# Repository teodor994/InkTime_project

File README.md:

<h1 align="center">InkTime Watch</h1>

<br>
<br>

This document presents the design and implementation details of the InkTime smartwatch project, covering both the hardware architecture and mechanical integration.

In the following sections, you will find comprehensive documentation including the schematic, PCB layout, component selection, and 3D assembly of the device.

<br> 

## Block Diagram

```text

                                +----------------------+
                                |        USB-C         |
                                |   Power / USB Data   |
                                +----------+-----------+
                                           |
                                           v
                                +----------------------+
                                |   ESD Protection     |
                                |    USBLC6-2SC6Y      |
                                +----------+-----------+
                                           |
                                           v
                                +----------------------+
                                |   Li-Po Charger      |
                                |    BQ25180YBGR       |
                                +----+------------+----+
                                     |            |
                                     |            +--------------------+
                                     |                                 |
                                     v                                 v
                           +-------------------+             +-------------------+
                           |   Li-Po Battery   |             |   Fuel Gauge      |
                           |     LP502030      |<-- I2C ---> |    MAX17048       |
                           +---------+---------+             +-------------------+
                                     |
                                     v
                           +-------------------+
                           | Buck-Boost DC/DC  |
                           |    RT6160AWSC     |
                           +---------+---------+
                                     |
                                   3V3 / VREG
                                     |
        +----------------------------+------------------------------+
        |                            |                              |
        v                            v                              v
+---------------+          +-------------------+          +-------------------+
|   nRF52840    |<--I2C--->|      BMA421       |<--I2C--->|     DRV2605       |
|   BLE MCU     |          |       IMU         |          |   Haptic Driver   |
+-------+-------+          +-------------------+          +---------+---------+
        |                                                              |
        | SPI + GPIO                                                    v
        v                                                      +----------------+
+-------------------+                                          | Vibration Motor|
| 1.54" E-Paper     |                                          |     (Shaker)   |
| via FPC Connector |                                          +----------------+
+-------------------+
        |
        +--> Dedicated E-Paper Power Stage:
             MOSFETs + Schottky Diodes + Inductors + Capacitors

```

## Hardware Functionality

###  Microcontroller

The system is built around a Nordic **nRF52840** SoC  
*(Arm Cortex-M4F @ 64 MHz, 1 MB Flash, 256 kB RAM)*.

This component was chosen because it integrates:
- a **2.4 GHz radio (Bluetooth Low Energy)**
- a **USB 2.0 full-speed controller**

 This allows both:
- wireless communication (BLE)
- USB-C data connectivity  

without requiring any external transceiver.

The MCU operates using two external crystals:
- **32 MHz HF crystal (XC1/XC2)** → CPU + radio
- **32.768 kHz LF crystal (XL1/XL2)** → RTC + low-power timing  

> Accurate timekeeping is critical for a watch, therefore the LFXO is mandatory.

An on-board **2.4 GHz chip antenna (2450AT18B100E)** is:
- placed at the edge of the PCB  
- isolated via a **ground keep-out zone**  

The antenna is connected to the `ANT` pin through a matching network.

---

### Display — E-Paper (SPI)

A reflective **e-paper display** is controlled via the SPI interface:

- `SCK` → P0.02  
- `MOSI` → P0.03  
- `CS` → P0.05  

Additional control signals:
- `EPD_DC` (P0.15) → command/data selection  
- `EPD_RST` (P0.16) → hardware reset  
- `EPD_BUSY` (P0.17) → busy status input  

The display is connected using a **24-pin FPC connector**.

#### Power Optimization
E-paper displays consume power **only during refresh**.

To optimize energy consumption:
- the display power rail is gated using a **PFET**
- controlled by `P1.01`

This allows:
- complete power shutdown between updates  
- significantly extended battery life (days instead of hours)

---

### IMU — BMA421 (I²C)

The **Bosch BMA421** accelerometer provides:
- 3-axis acceleration data  
- built-in **step counting functionality**

Connected via the shared I²C bus.

Interrupt lines:
- `IMU_INT1` → P0.08  
- `IMU_INT2` → P1.08  

These allow:
- wake-up from deep sleep  
- event-driven processing (no polling required)

---

### Haptics — DRV2605 (I²C)

The **TI DRV2605L** controls a vibration motor (LRA/ERM).

Key features:
- I²C configuration interface  
- internal ROM with predefined haptic effects  

The MCU only sends:
> “play effect N” commands  

instead of generating waveforms.

Control signal:
- `HAPTIC_EN` → P0.12  

Allows full shutdown of the driver when idle.

---

### Power Management  
**BQ25180 + MAX17048 + RT6160**

#### USB Input
- USB-C provides **5V input**
- protected by **USBLC6-2SC6Y (ESD protection)**
- includes **5.1 kΩ CC pull-down resistors** → device configured as sink

---

#### Battery Charging — BQ25180
Handles:
- Li-Po charging (CC/CV)
- power path management (USB ↔ battery switching)

Communication:
- I²C interface
- interrupt line: `PMIC_INT` → P0.11  

---

#### Voltage Regulation — RT6160
- Buck-boost converter generating stable **3.3V (VREG)**

Why buck-boost:
- battery range: **3.0V – 4.2V**
- ensures stable output across full discharge cycle

---

#### Fuel Gauge — MAX17048
Provides:
- battery percentage
- voltage monitoring

Uses **ModelGauge algorithm**:
- no current sense resistor required

Communication:
- I²C interface  
- `ALERT` → P1.10 (threshold events)

---

### Inputs — Buttons

Three user buttons connected as:
- `P0.13`
- `P0.14`
- `P1.02`

Characteristics:
- active-low configuration  
- RC debounce  
- internal pull-ups used  

Support:
- GPIOTE interrupts  
- wake-up from System OFF

---

### Shared I²C Bus

All I²C peripherals share the same bus:

Devices:
- BMA421 (IMU)
- MAX17048 (fuel gauge)
- DRV2605L (haptics)
- BQ25180 (charger)

Bus lines:
- `SDA` → P0.06  
- `SCL` → P0.07  

Pull-ups:
- **3.3 kΩ to 3V3**

Operating mode:
- **400 kHz (Fast Mode)**

Sufficient for low-bandwidth sensor communication.

---

### Debug Interface

Programming and debugging via SWD:

- `SWDCLK`
- `SWDIO`
- optional `SWO` → P1.00  

Connector:
- **Tag-Connect TC2030 footprint**

Advantage:
- no bulky header required (important for wearable design)

---

### Expected Capabilities

Based on this hardware, the system supports:

- accurate timekeeping using RTC + LFXO  
- rendering UI on e-paper display  
- step detection & gesture sensing  
- haptic feedback via vibration motor  
- BLE communication with a smartphone  
- USB connectivity for power and data  
- real-time battery monitoring  

The design enables a **low-power wearable device** with multi-day battery life.

## Pinout Table

| Pin | Signal | Direction | Peripheral | Description |
|-----|--------|-----------|------------|-------------|
| P0.02 | SPI_SCK | Output | E-Paper Display | SPI clock |
| P0.03 | SPI_MOSI | Output | E-Paper Display | SPI data out |
| P0.05 | EPD_CS | Output | E-Paper Display | Chip select |
| P0.06 | SDA | Bidir | Fuel Gauge, Charger, IMU, Haptics | Shared I2C data |
| P0.07 | SCL | Output | Fuel Gauge, Charger, IMU, Haptics | Shared I2C clock |
| P0.08 | IMU_INT1 | Input | IMU (BMA421) | Interrupt line 1 |
| P0.11 | PMIC_INT | Input | Charger (BQ25180) | Fault/status interrupt |
| P0.12 | HAPTIC_EN | Output | Haptics (DRV2605) | Driver enable |
| P0.13 | — | Input | Button 1 | User button |
| P0.14 | — | Input | Button 2 | User button |
| P0.15 | EPD_DC | Output | E-Paper Display | Data/command select |
| P0.16 | EPD_RST | Output | E-Paper Display | Display reset |
| P0.17 | EPD_BUSY | Input | E-Paper Display | Busy status |
| P0.18 | RESET | Input | — | System reset |
| P1.00 | SWO | Output | Debug (pad) | SWD trace output |
| P1.01 | — | Output | EPD power gate | EPD power control |
| P1.02 | — | Input | Button 3 | User button |
| P1.08 | IMU_INT2 | Input | IMU (BMA421) | Interrupt line 2 |
| P1.10 | ALERT | Input | Fuel Gauge (MAX17048) | UV/OV alert |
| D+ | D+ | Bidir | USB-C connector | USB data+ |
| D− | D- | Bidir | USB-C connector | USB data− |
| XL1/XL2 | — | — | 32.768 kHz crystal | Low-frequency clock |
| XC1/XC2 | — | — | 32 MHz crystal | High-frequency clock |
| SWDCLK | SWDCLK | Input | Debug (pad) | SWD clock |
| SWDIO | SWDIO | Bidir | Debug (pad) | SWD data |
| ANT | RF | Output | 2.4 GHz antenna | Wireless antenna feed |

## Bill of Materials (BOM)

| Part Name | Qty | Link (Order + Datasheet) |
| :-- | :--: | :--: |
| NRF52840-QIAA-R7 | 1 | [Link](https://jlcpcb.com/partdetail/NordicSemicon-NRF52840_QIAAR7/C1851953) |
| BMA421 | 1 | [Link](https://jlcpcb.com/partdetail/BoschSensortec-BMA421/C5242966) |
| DRV2605YZFR | 1 | [Link](https://jlcpcb.com/partdetail/TexasInstruments-DRV2605YZFR/C81079) |
| BQ25180YBGR | 1 | [Link](https://jlcpcb.com/partdetail/TexasInstruments-BQ25180YBGR/C3682423) |
| MAX17048G+T10 | 1 | [Link](https://jlcpcb.com/partdetail/2777647-MAX17048GT10/C2682616) |
| RT6160AWSC | 1 | [Link](https://jlcpcb.com/partdetail/RichtekTech-RT6160AWSC/C7065276) |
| USBLC6-2SC6Y | 1 | [Link](https://jlcpcb.com/partdetail/TECHPUBLIC-USBLC62SC6Y/C5310974) |
| KH-TYPE-C-16P | 1 | [Link](https://jlcpcb.com/partdetail/Shenzhen_KinghelmElec-KH_TYPE_C16P/C709357) |
| 2450AT18B100E | 1 | [Link](https://jlcpcb.com/partdetail/JohansonDielectrics-2450AT18B100E/C2917717) |
| SI1308EDL-T1-GE3 | 1 | [Link](https://jlcpcb.com/partdetail/VishayIntertech-SI1308EDL_T1GE3/C469327) |
| DMG2305UX-7 | 1 | [Link](https://jlcpcb.com/partdetail/DiodesIncorporated-DMG2305UX7/C150470) |
| 5034802400 | 1 | [Link](https://jlcpcb.com/partdetail/MOLEX-5034802400/C122434) |
| EVPAKE31A | 3 | [Link](https://jlcpcb.com/partdetail/PANASONIC-EVPAKE31A/C569760) |
| NX2016SA-32MHZ-STD-CZS-5 | 1 | [Link](https://jlcpcb.com/partdetail/NDK-NX2016SA_32MHZ_STD_CZS5/C843260) |
| CM8V-T1A-32.768KHZ-9PF-20PPM-TB-QA | 1 | [Link](https://jlcpcb.com/partdetail/C5366546) |
| SDFL1608S100KTF | 1 | [Link](https://jlcpcb.com/partdetail/Sunlord-SDFL1608S100KTF/C1035) |
| SDCL1005C15NJTDF | 1 | [Link](https://jlcpcb.com/partdetail/Sunlord-SDCL1005C15NJTDF/C27143) |
| SDCL1005C3N9STDF | 1 | [Link](https://jlcpcb.com/partdetail/Sunlord-SDCL1005C3N9STDF/C14033) |
| FTC252012SR47MBCA | 1 | [Link](https://jlcpcb.com/partdetail/6763488-FTC252012SR47MBCA/C5832368) |
| 744043680 | 1 | [Link](https://jlcpcb.com/partdetail/WurthElektronik-744043680/C2045671) |
| MBR0530 | 3 | [Link](https://jlcpcb.com/partdetail/78464-MBR0530/C77336) |
| GRM033R61A104KE15D | 5 | [Link](https://jlcpcb.com/partdetail/MurataElectronics-GRM033R61A104KE15D/C76934) |
| GRM155R60J226ME11D | 2 | [Link](https://jlcpcb.com/partdetail/408393-GRM155R60J226ME11D/C415703) |
| GRM155R61H105KE05D | 9 | [Link](https://jlcpcb.com/partdetail/1609005-GRM155R61H105KE05D/C1518208) |
| GRM0335C1H1R0BA01D | 2 | [Link](https://jlcpcb.com/partdetail/MurataElectronics-GRM0335C1H1R0BA01D/C85893) |
| GRM0335C1H101JA01D | 1 | [Link](https://jlcpcb.com/partdetail/MurataElectronics-GRM0335C1H101JA01D/C76922) |
| CGA0402X5R475M250GT | 1 | [Link](https://jlcpcb.com/partdetail/HRE-CGA0402X5R475M250GT/C6119795) |
| CL05A475MP5NRNC | 5 | [Link](https://jlcpcb.com/partdetail/24469-CL05A475MP5NRNC/C23733) |
| CL05A105KA5NQNC | 6 | [Link](https://jlcpcb.com/partdetail/53938-CL05A105KA5NQNC/C52923) |
| CL05A106MQ5NUNC | 3 | [Link](https://jlcpcb.com/partdetail/16204-CL05A106MQ5NUNC/C15525) |
| CC0201KRX5R7BB473 | 1 | [Link](https://jlcpcb.com/partdetail/YAGEO-CC0201KRX5R7BB473/C505465) |
| 0201X104K100NT | 5 | [Link](https://jlcpcb.com/partdetail/270391-0201X104K100NT/C284966) |
| 0201WMF220KTEE | 1 | [Link](https://jlcpcb.com/partdetail/479910-0201WMF220KTEE/C473517) |
| 0201WMJ0000TEE | 3 | [Link](https://jlcpcb.com/partdetail/259867-0201WMJ0000TEE/C270337) |
| 0201WMJ0332TEE | 2 | [Link](https://jlcpcb.com/partdetail/259848-0201WMJ0332TEE/C270318) |
| 0201CG120J500NT | 4 | [Link](https://jlcpcb.com/partdetail/51400-0201CG120J500NT/C50391) |
| CR0201FH5101G | 2 | [Link](https://jlcpcb.com/partdetail/LIZElec-CR0201FH5101G/C100142) |
| CPF0201D10KC1 | 6 | [Link](https://jlcpcb.com/partdetail/TEConnectivity-CPF0201D10KC1/C4187156) |
| UCR006YVPFLR470 | 1 | [Link](https://jlcpcb.com/partdetail/ROHMSemicon-UCR006YVPFLR470/C2089071) |

## Design Details

### Schematic and Components

The reference schematic was carefully reviewed and validated against the datasheets of each individual component. Any inconsistencies identified during this process were analyzed and corrected, most of them originating from outdated reference designs used in the initial schematic.

---

### PCB Layout and Routing

The PCB was designed in accordance with the manufacturing constraints specified by JLCPCB for standard rigid PCB assembly.

A ground pour was implemented on the top layer and connected to the main ground plane using via stitching. Additional manual stitching was applied in sensitive areas, particularly around the antenna feed line, to improve signal integrity.

Teardrops were added to most trace junctions to enhance mechanical reliability. Due to limitations in Fusion when generating teardrops for off-grid or rotated components, some shapes—especially those near the MCU (placed at a 45-degree angle)—were manually refined to ensure proper geometry.

Given the limited available space and the minimum recommended silkscreen text size of 1 mm, an indexed labeling approach was used. Larger components, ICs, and important pads were labeled directly on the silkscreen, while smaller areas rely on the legend.

To ensure mechanical robustness, relatively large internal annular rings were maintained. As a consequence, certain unused pins of the MCU were masked to prevent unintended electrical connections with traces routed underneath.

VIA-in-pad (ViP) technology was used extensively for compact multi-pin SMD components. Any DRC warnings related to ViP clearances were manually reviewed and accepted where appropriate.

Special attention was given to spatial constraints such as:
- antenna keep-out zone
- crystal oscillator trace length
- maximizing distance between the IMU and the shaker motor

Additionally, all decoupling capacitors were placed as close as possible to their respective power pins.

The USB differential pair (D+ and D−) was routed carefully, maintaining approximately equal lengths and minimal spacing between the traces to preserve signal integrity.

---

### 3D Design

Accurate 3D models for all components were integrated into the PCB assembly in order to validate the mechanical design.

The complete enclosure assembly was analyzed to detect any potential mechanical interferences. A possible issue was identified regarding the battery height specified in its datasheet, as the available space in the lower part of the enclosure may be insufficient.

At this stage, the enclosure design was left unchanged, with the intention of validating this aspect during the physical prototyping phase.

## Renders

### PCB 2D

### PCB 3D

### Assembly

### Exploded View

### Without Display

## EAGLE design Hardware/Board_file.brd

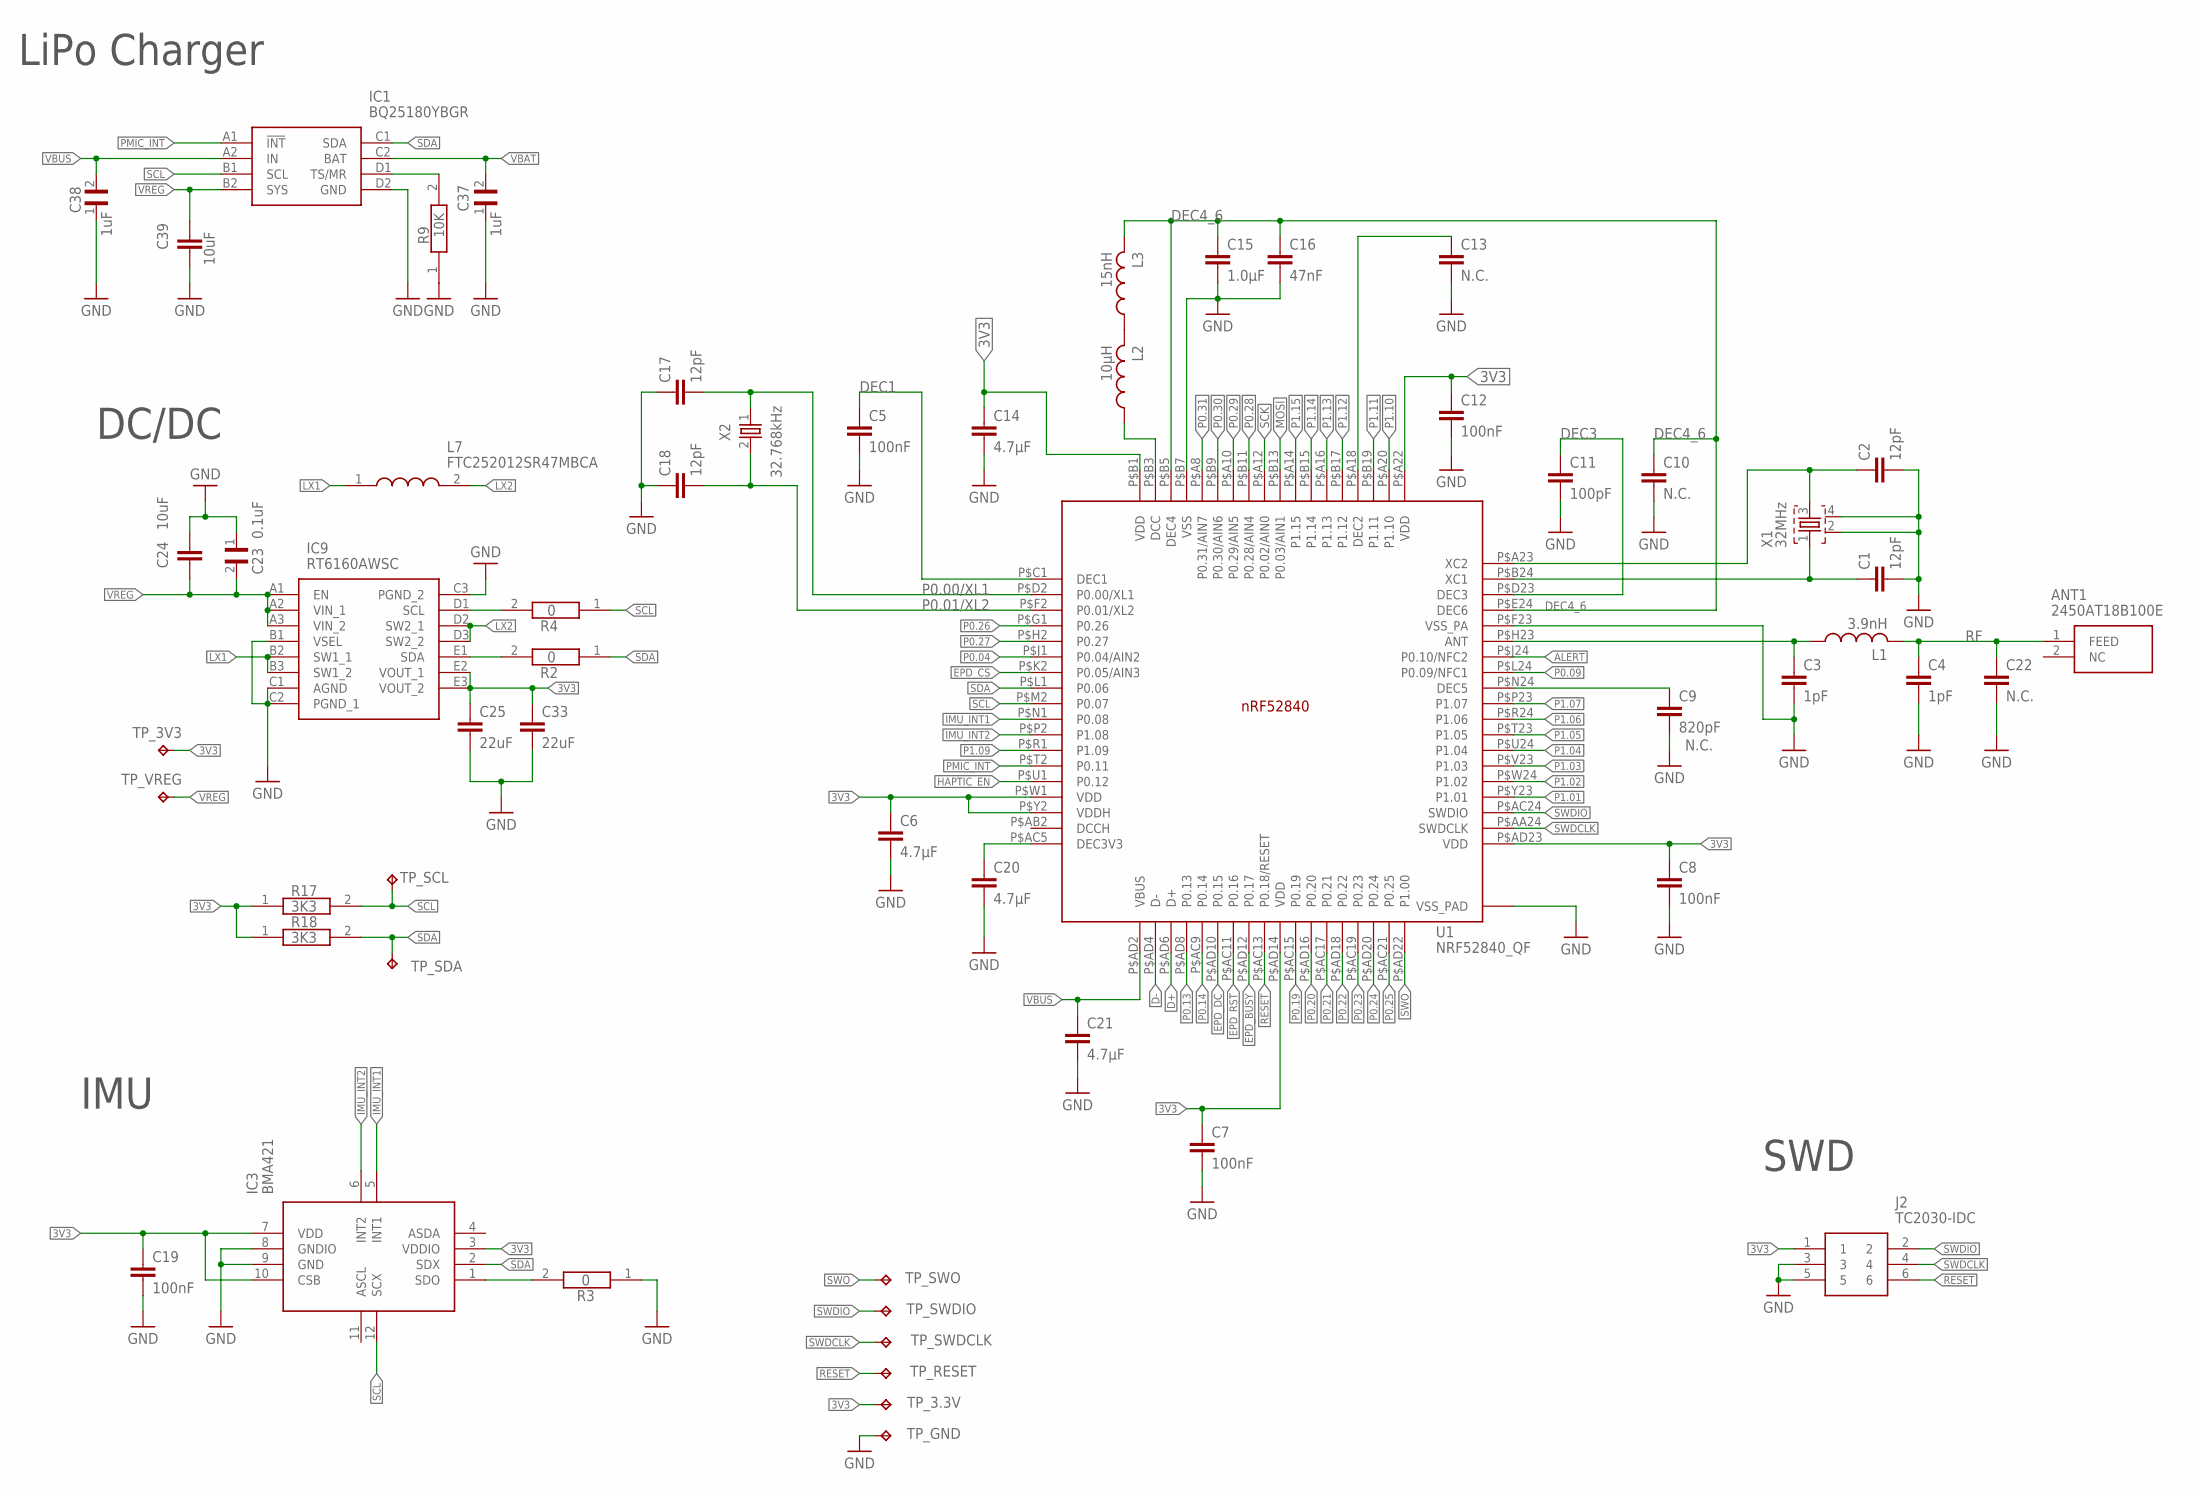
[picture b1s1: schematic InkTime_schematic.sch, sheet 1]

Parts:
ANT1: 2450AT18B100E; 2450AT18B100E_ANTC3216X140N
C1, C2, C17, C18: 12pF; NORDIC_NRF_3_RESC0201_L
C3, C4: 1pF; NORDIC_NRF_3_RESC0201_L
C5, C7, C8, C12, C19: 100nF; NORDIC_NRF_3_RESC0201_L
C6, C14, C20, C21: 4.7µF; NORDIC_NRF_3_RESC0201_L
C9: 820pF; NORDIC_NRF_3_RESC0201_L
C10, C13, C22: N.C.; NORDIC_NRF_3_RESC0201_L
C11: 100pF; NORDIC_NRF_3_RESC0201_L
C15: 1.0µF; NORDIC_NRF_3_RESC0201_L
C16: 47nF; NORDIC_NRF_3_RESC0201_L
C23: 0.1uF; GRM011R60J152KE01L_1_0201
C24, C39: 10uF; NORDIC_NRF_3_RESC0201_L
C25, C33: 22uF; NORDIC_NRF_3_RESC0201_L
C37: 1uF; GRM011R60J152KE01L_1_0201
C38: 1uF; GRM011R60J152KE01L_2_CAPC0201X13N
IC1: BQ25180YBGR; BQ25180YBGR_BGA8C40P2X4_100X155X50
IC3: BMA421; BMA423_BMA423
IC9: RT6160AWSC; RT6160AWSC_BGA15C40P3X5_140X230X60
J2: TC2030-IDC; TC2030-IDC_TC2030IDC
L1: 3.9nH; NORDIC_NRF_2_RESC0402_L
L2: 10µH; NORDIC_NRF_2_RESC0402_L
L3: 15nH; NORDIC_NRF_2_RESC0402_L
L7: FTC252012SR47MBCA; MLP2016SR47MT0S1_INDC2016X100N
R2, R3, R4: 0; CPF0201D7K68C1_0201
R9: 10K; CPF0201D7K68C1_0201
R17, R18: 3K3; CPF0201D7K68C1_0201
TP_3.3V, TP_3V3: HECTOR_WATCH_1_TPTP20R; HECTOR_WATCH_1_TP20R
TP_GND: HECTOR_WATCH_1_TPTP20R; HECTOR_WATCH_1_TP20R
TP_RESET: HECTOR_WATCH_1_TPTP20R; HECTOR_WATCH_1_TP20R
TP_SCL: HECTOR_WATCH_1_TPTP20R; HECTOR_WATCH_1_TP20R
TP_SDA: HECTOR_WATCH_1_TPTP20R; HECTOR_WATCH_1_TP20R
TP_SWDCLK: HECTOR_WATCH_1_TPTP20R; HECTOR_WATCH_1_TP20R
TP_SWDIO: HECTOR_WATCH_1_TPTP20R; HECTOR_WATCH_1_TP20R
TP_SWO: HECTOR_WATCH_1_TPTP20R; HECTOR_WATCH_1_TP20R
TP_VREG: HECTOR_WATCH_1_TPTP20R; HECTOR_WATCH_1_TP20R
U1: NRF52840_QF; NORDIC_NRF_4_AQFN50P700X700X85_HS-74N
X1: 32MHz; NORDIC_NRF_BT-XTAL_2016_N
X2: 32.768kHz; NORDIC_NRF_1_XTAL_3215_N

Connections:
3V3: C6.1, C7.1, C8.1, C12.1, C14.1, C19.1, C25.1, C33.1, IC3.3 (VDDIO), IC3.7 (VDD), IC3.10 (CSB), IC9.E2 (VOUT_1), IC9.E3 (VOUT_2), J2.1, R17.1, R18.1, TP_3.3V.TP, TP_3V3.TP, U1.P$A22 (VDD), U1.P$AD14 (VDD), U1.P$AD23 (VDD), U1.P$B1 (VDD), U1.P$W1 (VDD), U1.P$Y2 (VDDH); also elsewhere on the board
ALERT: U1.P$J24 (P0.10/NFC2); also elsewhere on the board
D+: U1.P$AD6 (D+); also elsewhere on the board
D-: U1.P$AD4 (D-); also elsewhere on the board
DEC1: C5.1, U1.P$C1 (DEC1)
DEC3: C11.1, U1.P$D23 (DEC3)
DEC4_6: C10.1, C15.1, C16.1, L3.2, U1.P$B5 (DEC4), U1.P$E24 (DEC6)
EPD_BUSY: U1.P$AD12 (P0.17); also elsewhere on the board
EPD_CS: U1.P$K2 (P0.05/AIN3); also elsewhere on the board
EPD_DC: U1.P$AD10 (P0.15); also elsewhere on the board
EPD_RST: U1.P$AC11 (P0.16); also elsewhere on the board
GND: C1.2, C2.2, C3.2, C4.2, C5.2, C6.2, C7.2, C8.2, C9.2, C10.2, C11.2, C12.2, C13.2, C14.2, C15.2, C16.2, C17.1, C18.1, C19.2, C20.2, C21.2, C22.2, C23.1, C24.1, C25.2, C33.2, C37.1, C38.1, C39.2, IC1.D2 (GND), IC3.8 (GNDIO), IC3.9 (GND), IC9.B1 (VSEL), IC9.C1 (AGND), IC9.C2 (PGND_1), IC9.C3 (PGND_2), J2.3, J2.5, R3.1, R9.1, TP_GND.TP, U1.P$74 (VSS_PAD), U1.P$75 (VSS_PAD), U1.P$76 (VSS_PAD), U1.P$77 (VSS_PAD), U1.P$78 (VSS_PAD), U1.P$79 (VSS_PAD), U1.P$80 (VSS_PAD), U1.P$81 (VSS_PAD), U1.P$82 (VSS_PAD), U1.P$83 (VSS_PAD), U1.P$84 (VSS_PAD), U1.P$85 (VSS_PAD), U1.P$86 (VSS_PAD), U1.P$87 (VSS_PAD), U1.P$88 (VSS_PAD), U1.P$89 (VSS_PAD), U1.P$90 (VSS_PAD), U1.P$B7 (VSS), U1.P$F23 (VSS_PA), X1.2, X1.4; also elsewhere on the board
HAPTIC_EN: U1.P$U1 (P0.12); also elsewhere on the board
IMU_INT1: IC3.5 (INT1), U1.P$N1 (P0.08)
IMU_INT2: IC3.6 (INT2), U1.P$P2 (P1.08)
LX1: IC9.B2 (SW1_1), IC9.B3 (SW1_2), L7.1
LX2: IC9.D2 (SW2_1), IC9.D3 (SW2_2), L7.2
MOSI: U1.P$B13 (P0.03/AIN1); also elsewhere on the board
unnamed: IC3.1 (SDO), R3.2
unnamed: IC1.D1 (TS/MR), R9.2
unnamed: IC9.D1 (SCL), R4.2
unnamed: IC9.E1 (SDA), R2.2
unnamed: C20.1, U1.P$AC5 (DEC3V3)
unnamed: L2.1, U1.P$B3 (DCC)
unnamed: L2.2, L3.1
unnamed: C13.1, U1.P$A18 (DEC2)
unnamed: C9.1, U1.P$N24 (DEC5)
unnamed: C3.1, L1.1, U1.P$H23 (ANT)
unnamed: C2.1, U1.P$A23 (XC2), X1.3
unnamed: C1.1, U1.P$B24 (XC1), X1.1
P0.00/XL1: C17.2, U1.P$D2 (P0.00/XL1), X2.1
P0.01/XL2: C18.2, U1.P$F2 (P0.01/XL2), X2.2
P0.04: U1.P$J1 (P0.04/AIN2)
P0.09: U1.P$L24 (P0.09/NFC1)
P0.13: U1.P$AD8 (P0.13); also elsewhere on the board
P0.14: U1.P$AC9 (P0.14); also elsewhere on the board
P0.19: U1.P$AC15 (P0.19)
P0.20: U1.P$AD16 (P0.20)
P0.21: U1.P$AC17 (P0.21)
P0.22: U1.P$AD18 (P0.22)
P0.23: U1.P$AC19 (P0.23)
P0.24: U1.P$AD20 (P0.24)
P0.25: U1.P$AC21 (P0.25)
P0.26: U1.P$G1 (P0.26)
P0.27: U1.P$H2 (P0.27)
P0.28: U1.P$B11 (P0.28/AIN4)
P0.29: U1.P$A10 (P0.29/AIN5)
P0.30: U1.P$B9 (P0.30/AIN6)
P0.31: U1.P$A8 (P0.31/AIN7)
P1.01: U1.P$Y23 (P1.01); also elsewhere on the board
P1.02: U1.P$W24 (P1.02); also elsewhere on the board
P1.03: U1.P$V23 (P1.03)
P1.04: U1.P$U24 (P1.04)
P1.05: U1.P$T23 (P1.05)
P1.06: U1.P$R24 (P1.06)
P1.07: U1.P$P23 (P1.07)
P1.09: U1.P$R1 (P1.09)
P1.10: U1.P$A20 (P1.10)
P1.11: U1.P$B19 (P1.11)
P1.12: U1.P$B17 (P1.12)
P1.13: U1.P$A16 (P1.13)
P1.14: U1.P$B15 (P1.14)
P1.15: U1.P$A14 (P1.15)
PMIC_INT: IC1.A1 (!INT), U1.P$T2 (P0.11)
RESET: J2.6, TP_RESET.TP, U1.P$AC13 (P0.18/RESET)
RF: ANT1.1 (FEED), C4.1, C22.1, L1.2
SCK: U1.P$A12 (P0.02/AIN0); also elsewhere on the board
SCL: IC1.B1 (SCL), IC3.12 (SCX), R4.1, R17.2, TP_SCL.TP, U1.P$M2 (P0.07); also elsewhere on the board
SDA: IC1.C1 (SDA), IC3.2 (SDX), R2.1, R18.2, TP_SDA.TP, U1.P$L1 (P0.06); also elsewhere on the board
SWDCLK: J2.4, TP_SWDCLK.TP, U1.P$AC24 (SWDIO)
SWDIO: J2.2, TP_SWDIO.TP, U1.P$AA24 (SWDCLK)
SWO: TP_SWO.TP, U1.P$AD22 (P1.00)
VBAT: C37.2, IC1.C2 (BAT); also elsewhere on the board
VBUS: C21.1, C38.2, IC1.A2 (IN), U1.P$AD2 (VBUS); also elsewhere on the board
VREG: C23.2, C24.2, C39.1, IC1.B2 (SYS), IC9.A1 (EN), IC9.A2 (VIN_1), IC9.A3 (VIN_2), TP_VREG.TP

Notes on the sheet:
LiPo Charger
IMU
DC/DC
SWD

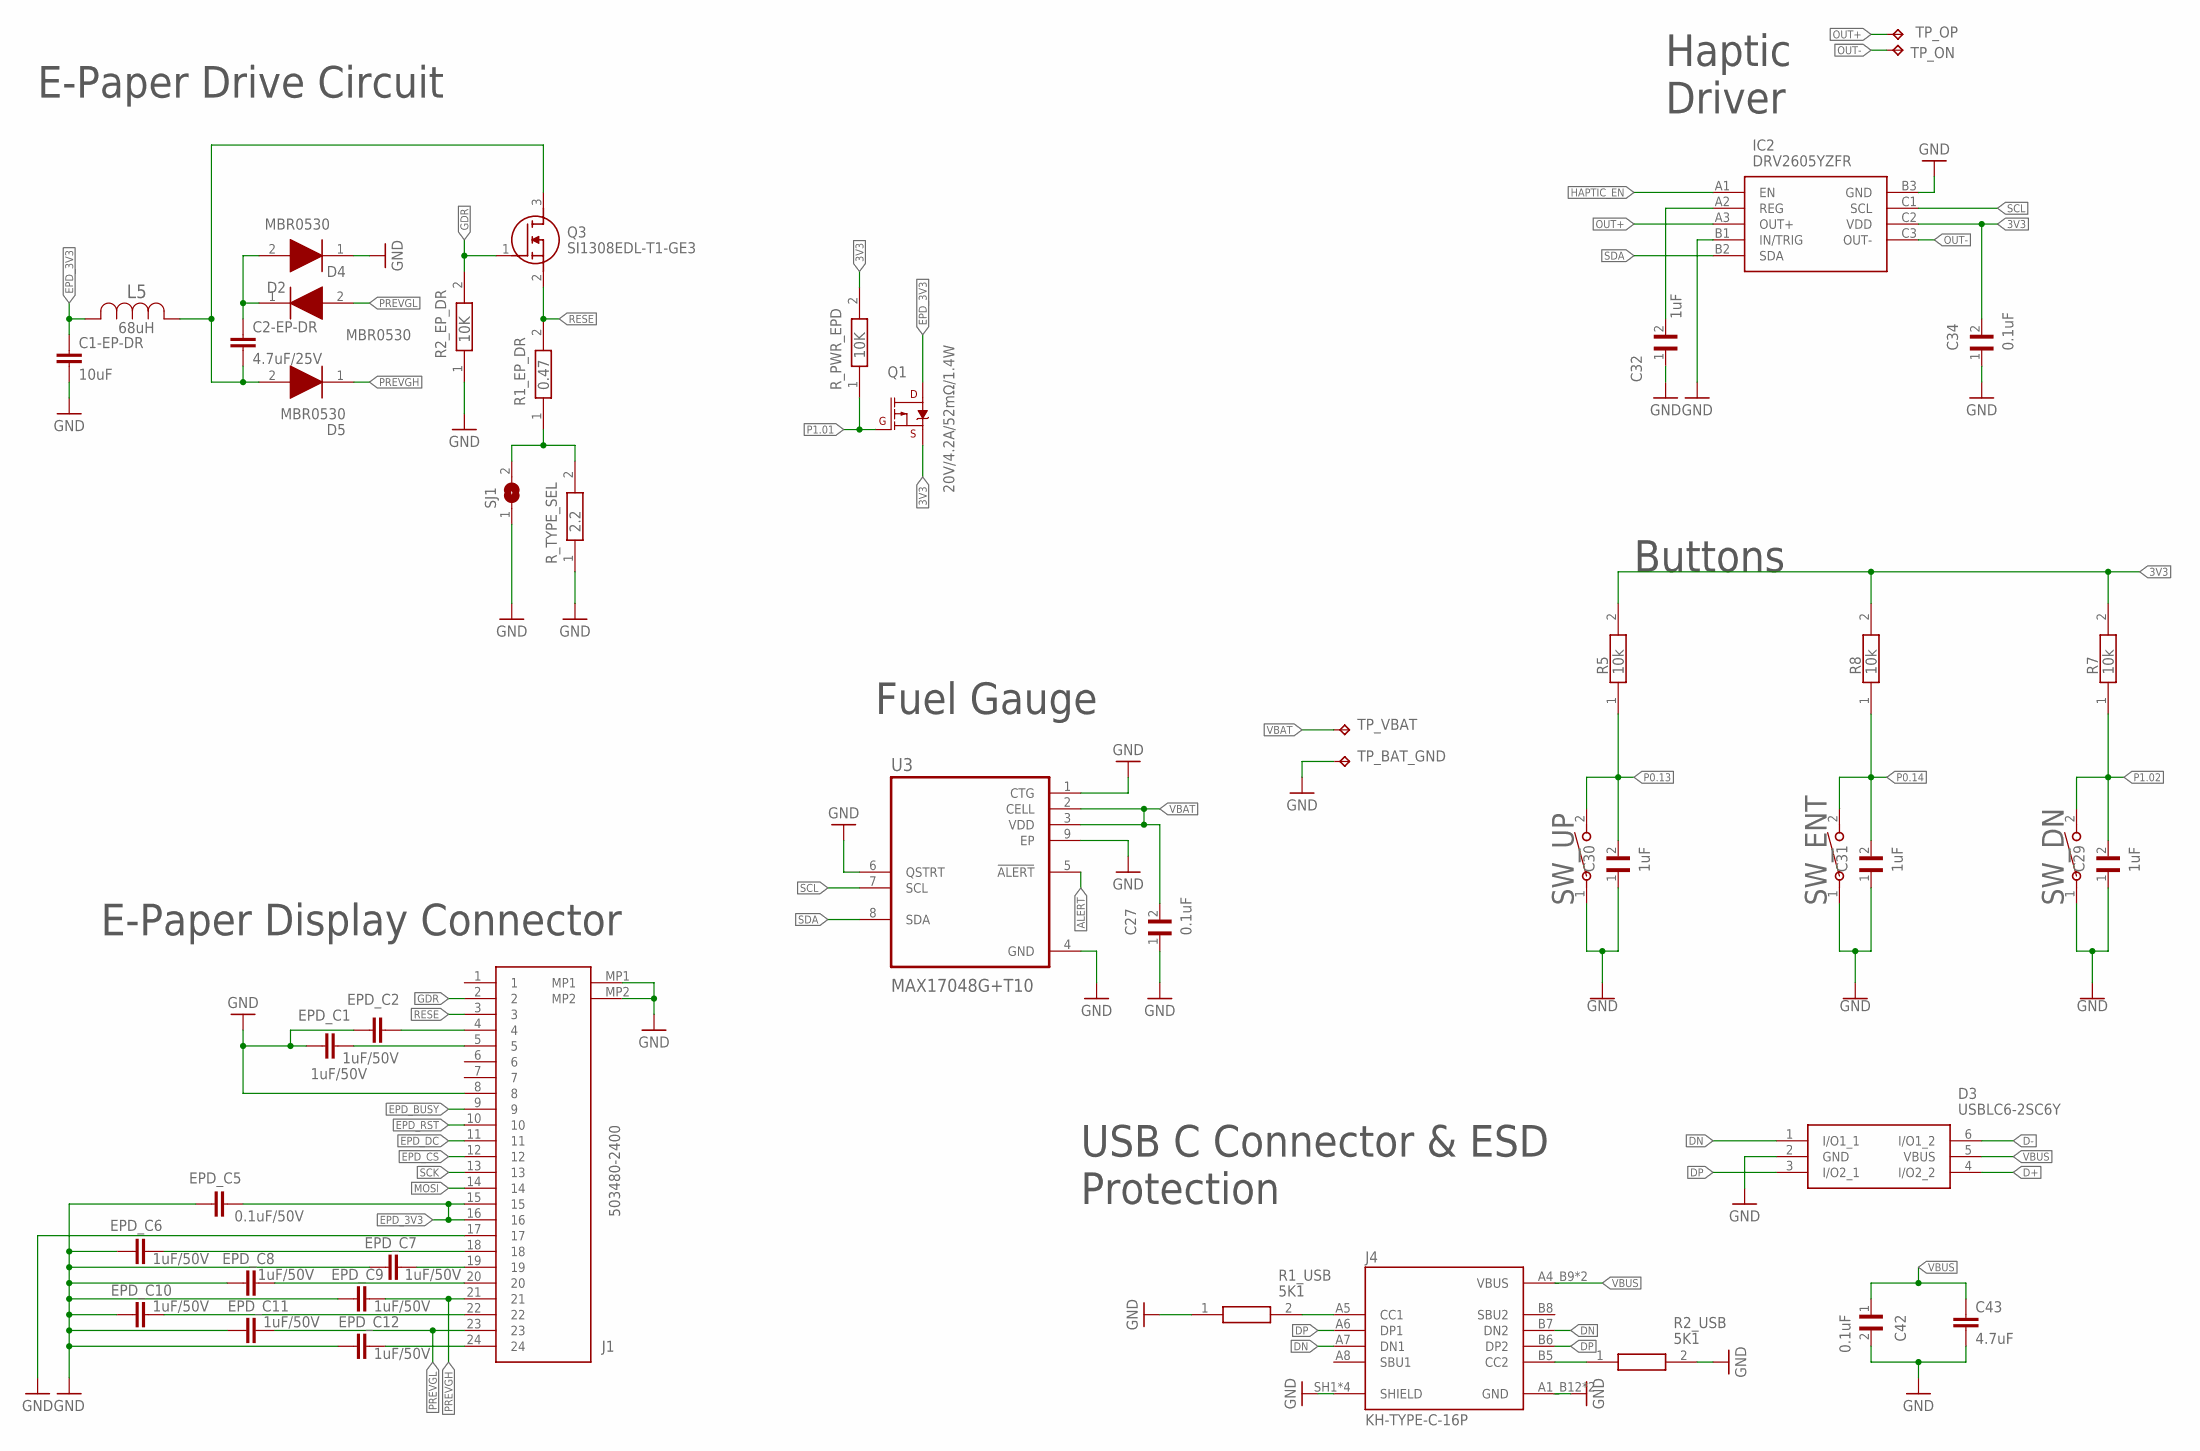
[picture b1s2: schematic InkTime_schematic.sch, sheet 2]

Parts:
C1-EP-DR: 10uF; NORDIC_NRF_3_RESC0201_L
C2-EP-DR: 4.7uF/25V; NORDIC_NRF_3_RESC0201_L
C27, C34, C42: 0.1uF; GRM011R60J152KE01L_1_0201
C29, C30, C31, C32: 1uF; GRM011R60J152KE01L_1_0201
C43: 4.7uF; NORDIC_NRF_3_RESC0201_L
D2, D4, D5: MBR0530; ESP32_C6_LIBRARY_5_SOD3716X135N
D3: USBLC6-2SC6Y; ESP32_C6_LIBRARY_3_SOT95P280X145-6N
EPD_C1, EPD_C2, EPD_C6, EPD_C7, EPD_C8, EPD_C9, EPD_C10, EPD_C11, EPD_C12: 1uF/50V; NORDIC_NRF_3_RESC0201_L
EPD_C5: 0.1uF/50V; NORDIC_NRF_3_RESC0201_L
IC2: DRV2605YZFR; DRV2605YZFR_BGA9C50P3X3_144X144X62
J1: 503480-2400; 503480-2400_5034802400
J4: KH-TYPE-C-16P; KH-TYPE-C-16P_KINGHELM_KH-TYPE-C-16P
L5: 68uH; ESP32_C6_LIBRARY_2_IND_4828-WE-TPC_WRE
Q1: 20V/4.2A/52mΩ/1.4W; ESP32_C6_LIBRARY_4_ESP32_C6_LIBRARY_4_ESP32_C6_LIBRARY_4_ES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
Q3: SI1308EDL-T1-GE3; ESP32_C6_LIBRARY_6_SOT65P210X110-3N
R1_EP_DR: 0.47; CPF0201D7K68C1_0201
R1_USB, R2_USB: 5K1; CPF0201D7K68C1_0201
R2_EP_DR: 10K; CPF0201D7K68C1_0201
R5, R7, R8: 10k; CPF0201D7K68C1_0201
R_PWR_EPD: 10K; CPF0201D7K68C1_0201
R_TYPE_SEL: 2.2; CPF0201D7K68C1_0201
SJ1: ESP32_C6_LIBRARY_7_JUMPER_SJ
SW_DN: 2025-10-22_07-23-44_LIBRARY_EVP-AKE31ASW_EVP-AKE3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; 2025-10-22_07-23-44_LIBRARY_SW_EVP-AKE31A_PAN
SW_ENT: 2025-10-22_07-23-44_LIBRARY_EVP-AKE31ASW_EVP-AKE3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; 2025-10-22_07-23-44_LIBRARY_SW_EVP-AKE31A_PAN
SW_UP: 2025-10-22_07-23-44_LIBRARY_EVP-AKE31ASW_EVP-AKE3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; 2025-10-22_07-23-44_LIBRARY_SW_EVP-AKE31A_PAN
TP_BAT_GND: HECTOR_WATCH_1_TPTP20R; HECTOR_WATCH_1_TP20R
TP_ON: HECTOR_WATCH_1_TPTP20R; HECTOR_WATCH_1_TP20R
TP_OP: HECTOR_WATCH_1_TPTP20R; HECTOR_WATCH_1_TP20R
TP_VBAT: HECTOR_WATCH_1_TPTP20R; HECTOR_WATCH_1_TP20R
U3: MAX17048G+T10; ESP32_C6_LIBRARY_SON50P200X200X80-9N

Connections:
3V3: C34.2, IC2.C2 (VDD), Q1.2 (S), R5.2, R7.2, R8.2, R_PWR_EPD.2; also elsewhere on the board
ALERT: U3.5 (!ALERT); also elsewhere on the board
D+: D3.4 (I/O2_2); also elsewhere on the board
D-: D3.6 (I/O1_2); also elsewhere on the board
DN: D3.1 (I/O1_1), J4.A7 (DN1), J4.B7 (DN2)
DP: D3.3 (I/O2_1), J4.A6 (DP1), J4.B6 (DP2)
EPD_3V3: C1-EP-DR.1, EPD_C5.2, J1.15, J1.16, L5.2, Q1.3 (D)
EPD_BUSY: J1.9; also elsewhere on the board
EPD_CS: J1.12; also elsewhere on the board
EPD_DC: J1.11; also elsewhere on the board
EPD_RST: J1.10; also elsewhere on the board
GDR: J1.2, Q3.1 (G), R2_EP_DR.2
GND: C1-EP-DR.2, C27.1, C29.1, C30.1, C31.1, C32.1, C34.1, C42.2, C43.2, D3.2 (GND), D4.1 (K), EPD_C1.1, EPD_C2.1, EPD_C5.1, EPD_C6.1, EPD_C7.1, EPD_C8.1, EPD_C9.1, EPD_C10.1, EPD_C11.1, EPD_C12.1, IC2.B1 (IN/TRIG), IC2.B3 (GND), J1.8, J1.17, J1.MP1, J1.MP2, J4.A1_B12 (GND), J4.A12_B1 (GND), J4.SH1 (SHIELD), J4.SH2 (SHIELD), J4.SH3 (SHIELD), J4.SH4 (SHIELD), R1_USB.1, R2_EP_DR.1, R2_USB.2, R_TYPE_SEL.1, SJ1.1, SW_DN.1, SW_ENT.1, SW_UP.1, TP_BAT_GND.TP, U3.1 (CTG), U3.4 (GND), U3.6 (QSTRT), U3.9 (EP); also elsewhere on the board
HAPTIC_EN: IC2.A1 (EN); also elsewhere on the board
MOSI: J1.14; also elsewhere on the board
unnamed: R1_EP_DR.1, R_TYPE_SEL.2, SJ1.2
unnamed: C2-EP-DR.2, D5.2 (A), L5.1, Q3.3 (D)
unnamed: C2-EP-DR.1, D2.1 (K), D4.2 (A)
unnamed: EPD_C2.2, J1.4
unnamed: EPD_C1.2, J1.5
unnamed: J4.B5 (CC2), R2_USB.1
unnamed: C32.2, IC2.A2 (REG)
unnamed: EPD_C6.2, J1.18
unnamed: EPD_C7.2, J1.19
unnamed: EPD_C8.2, J1.20
unnamed: EPD_C10.2, J1.22
unnamed: EPD_C12.2, J1.24
unnamed: J4.A5 (CC1), R1_USB.2
OUT+: IC2.A3 (OUT+), TP_OP.TP
OUT-: IC2.C3 (OUT-), TP_ON.TP
P0.13: C30.2, R5.1, SW_UP.2; also elsewhere on the board
P0.14: C31.2, R8.1, SW_ENT.2; also elsewhere on the board
P1.01: Q1.1 (G), R_PWR_EPD.1; also elsewhere on the board
P1.02: C29.2, R7.1, SW_DN.2; also elsewhere on the board
PREVGH: D5.1 (K), EPD_C9.2, J1.21
PREVGL: D2.2 (A), EPD_C11.2, J1.23
RESE: J1.3, Q3.2 (S), R1_EP_DR.2
SCK: J1.13; also elsewhere on the board
SCL: IC2.C1 (SCL), U3.7 (SCL); also elsewhere on the board
SDA: IC2.B2 (SDA), U3.8 (SDA); also elsewhere on the board
VBAT: C27.2, TP_VBAT.TP, U3.2 (CELL), U3.3 (VDD); also elsewhere on the board
VBUS: C42.1, C43.1, D3.5 (VBUS), J4.A4_B9 (VBUS), J4.A9_B4 (VBUS); also elsewhere on the board

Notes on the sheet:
E-Paper Drive Circuit
E-Paper Display Connector
Fuel Gauge
Haptic Driver
Buttons
USB C Connector & ESD Protection

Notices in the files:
parts and their libraries:
COPYRIGHT: Copyright (C) 2024 Ultra Librarian. All rights reserved.
COPYRIGHT: Copyright (C) 2025 Ultra Librarian. All rights reserved.
